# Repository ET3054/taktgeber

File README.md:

Einstellbarer Rechtecksignalgenerator (Taktgeber)
1. Projektbeschreibung
Im Rahmen dieses Projekts wurde ein einstellbarer Rechtecksignalgenerator entwickelt. Ziel des Projekts ist die Erzeugung eines Rechtecksignals mit einstellbarer Frequenz und Ausgangsamplitude.
Die elektrische Schaltung wurde mit KiCad 9 entworfen. Anschließend wurde auf Grundlage des Schaltplans eine vierlagige Leiterplatte (PCB) entwickelt.
Das Projekt umfasst den Schaltplan, das Leiterplattenlayout, die Bauteilliste (BOM) sowie die zugehörigen Fertigungsdaten.
2. Technische Daten
* Frequenzbereich: 1 Hz bis 1 kHz (Auslegungsziel)
* Ausgangsamplitude: 5 V bis 15 V (Auslegungsziel)
*Externe Versorgungsspannung:** 24 V DC oder ca. 17 V AC (Effektivwert, entsprechend 24 V Scheitelwert)
*Interne Versorgungsspannungen:** +18 V DC und +5 V DC
*Eingangsgleichrichtung:** Brückengleichrichter GBU4G mit anschließendem Glättungskondensator
* Leiterplatte: 4 Lagen
* Entwicklungssoftware: KiCad 9
3. Funktionsweise
3.1 Spannungsversorgung
Die Eingangsspannung wird zunächst über einen Brückengleichrichter (GBU4G) gleichgerichtet und anschließend durch einen Glättungskondensator stabilisiert.
Zwei Spannungsregler stellen die benötigten Versorgungsspannungen bereit:
* L7818CV: +18 V für die entsprechende Schaltungselektronik
* L7805CV: +5 V für den Mikrocontroller und das LCD
Zusätzlich wurde ein zweipoliger Anschluss J5 für einen externen Hauptschalter vorgesehen. Dieser ermöglicht die Unterbrechung einer Eingangsleitung vor dem Brückengleichrichter.
3.2 Signalerzeugung
Zur Erzeugung des Rechtecksignals wird der CMOS-Timer ICM7555IPAZ verwendet.
Die Frequenz wird über Widerstände, ein Potentiometer und umschaltbare Kondensatoren eingestellt.
Ein CD4013BE dient zur Frequenzteilung.
3.3 Einstellung der Ausgangsamplitude
Die Ausgangsstufe basiert auf einem LM358P.
Über ein Potentiometer wird die gewünschte Ausgangsamplitude eingestellt.
3.4 Mikrocontroller und Anzeige
Ein ATmega328P ist zur Verarbeitung der Signale und zur Ansteuerung eines 16×2-LCDs vorgesehen.
Das LCD dient zur Darstellung der relevanten Ausgangsgrößen.
Der Mikrocontroller soll separat programmiert und anschließend in seinen DIP-Sockel eingesetzt werden.
4. Leiterplattenaufbau
Die Leiterplatte wurde mit vier Kupferlagen entworfen:
Lage
Funktion
F.Cu
Signalleitungen und Versorgungsverbindungen
In1.Cu
GND-Fläche
In2.Cu
Getrennte Versorgungsflächen für +5 V und +18 V
B.Cu
Signalleitungen und Versorgungsverbindungen
Die Leiterplatte besitzt vier Montagebohrungen (H1–H4) zur mechanischen Befestigung.
Für die Hauptstromversorgung wurden entsprechend breitere Leiterbahnen vorgesehen.
5. Projektdateien
Das Repository enthält folgende Projekt- und Dokumentationsdateien:
* Flachbaugruppe.kicad_pro – KiCad-Projekteinstellungen
* Flachbaugruppe.kicad_sch – Elektrischer Schaltplan
* Flachbaugruppe.kicad_pcb – Vierlagiges Leiterplattenlayout
* Gerber/ – Gerber-Dateien, Bohrdateien und Bauteilpositionsdateien
* Flachbaugruppe_BOM_Final.csv – Aus KiCad exportierte Stückliste
* Rechtecksignalgenerator_BOM_Final.xlsx – Detaillierte Stückliste mit Hersteller- und Bauteilangaben
* Rechtecksignalgenerator_Fertigungsunterlagen.pdf – Fertigungs- und Bestückungsdokumentation
Die Fertigungsdokumentation wird an den aktuellen Entwicklungsstand angepasst.
6. Projektstatus
Der elektrische Schaltplan und das vierlagige Leiterplattenlayout wurden erstellt.
Im weiteren Entwicklungsverlauf wurde ein Anschluss für einen externen Hauptschalter (J5) ergänzt und in das PCB-Layout integriert.
Anschließend wurden die Leiterbahnen angepasst und die Design-Rule-Prüfung (DRC) durchgeführt.
Ergebnis der letzten DRC-Prüfung:
* 0 Leiterplattenverstöße
* 0 unverbundene Elemente
* 4 Hinweise zur Schaltplanparität aufgrund der ausschließlich auf der Leiterplatte vorhandenen Montagebohrungen H1–H4
Die Gerber-Dateien, Bohrdateien und Bauteilpositionsdateien wurden exportiert. Die Stückliste wurde aktualisiert.
Eine physische Fertigung und Bestückung der Leiterplatte sowie eine messtechnische Funktionsprüfung wurden bisher nicht durchgeführt.
7. Fazit
Im Rahmen des Projekts wurde ein vollständiger Schaltungsentwurf mit zugehörigem vierlagigem Leiterplattenlayout für einen einstellbaren Rechtecksignalgenerator erarbeitet.
Die Entwicklung umfasst die Spannungsversorgung, Signalerzeugung, Frequenzteilung, Ausgangsstufe sowie die vorgesehene Mikrocontroller- und LCD-Anbindung.
Die Projektdateien stehen zur weiteren Überprüfung, Weiterentwicklung und gegebenenfalls späteren Fertigung zur Verfügung.

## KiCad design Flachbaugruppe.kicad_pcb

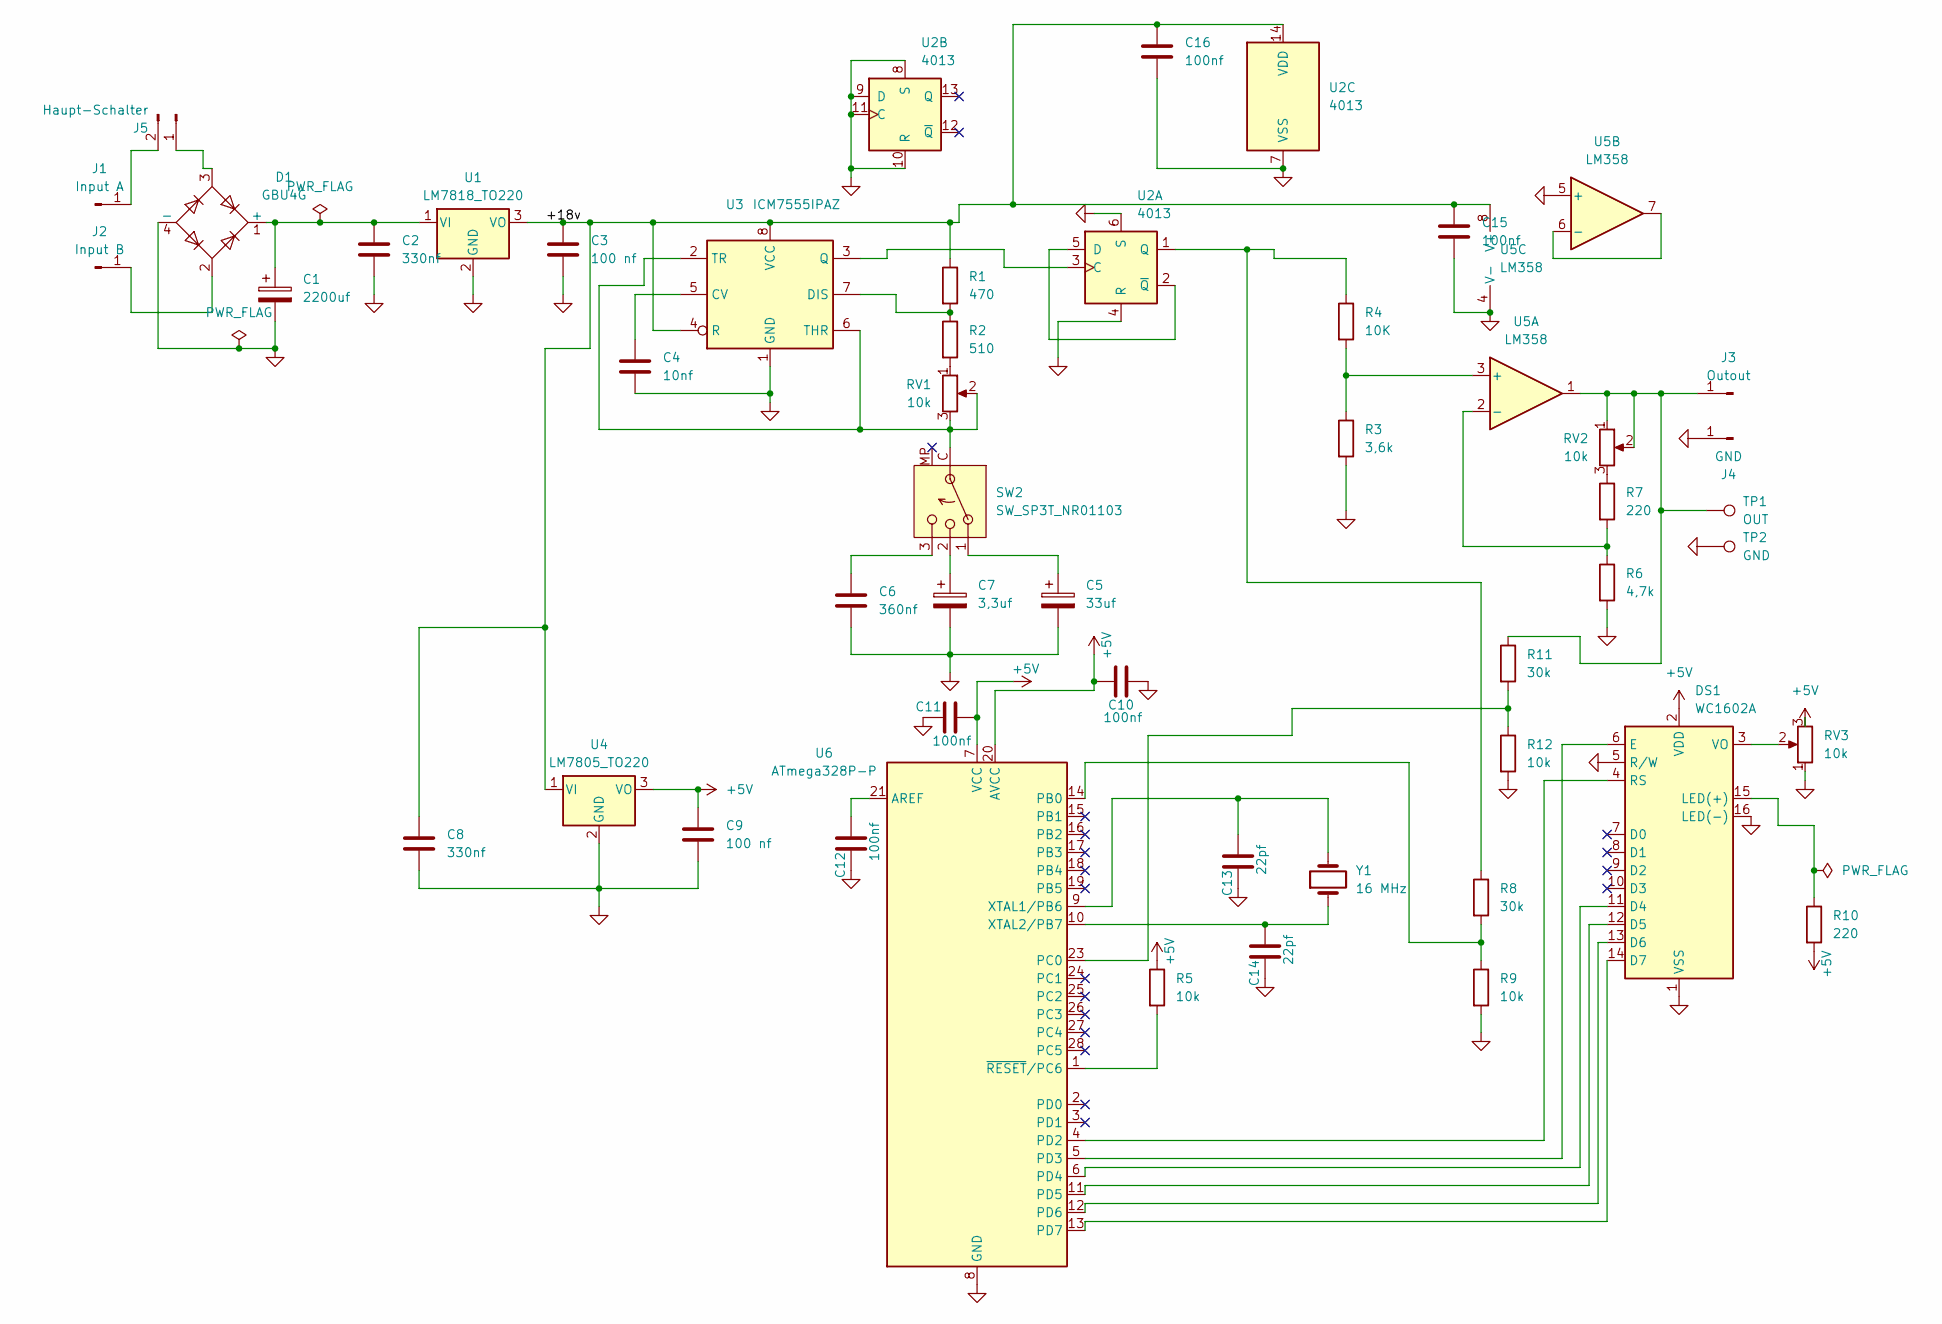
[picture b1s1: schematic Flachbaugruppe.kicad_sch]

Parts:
C1: 2200uf; CP_Radial_D16.0mm_P7.50mm
C2, C8: 330nf; C_0805_2012Metric
C3, C9: 100 nf; C_0805_2012Metric
C4: 10nf; C_0805_2012Metric
C5: 33uf; CP_Radial_D6.3mm_P2.50mm
C6: 360nf; C_0805_2012Metric
C7: 3,3uf; CP_Radial_D5.0mm_P2.00mm
C10, C11, C12, C15, C16: 100nf; C_0805_2012Metric
C13, C14: 22pf; C_0805_2012Metric
D1: GBU4G; Diode_Bridge_Vishay_GBU
DS1: WC1602A
J1: Input A; Banana_Jack_1Pin
J2: Input B; Banana_Jack_1Pin
J3: Outout; Banana_Jack_1Pin
J4: GND; Banana_Jack_1Pin
J5: Haupt-Schalter; TerminalBlock_MaiXu_MX126-5.0-02P_1x02_P5.00mm
R1: 470; R_0805_2012Metric
R2: 510; R_0805_2012Metric
R3: 3,6k; R_0805_2012Metric
R4: 10K; R_0805_2012Metric
R5, R9, R12: 10k; R_0805_2012Metric
R6: 4,7k; R_0805_2012Metric
R7, R10: 220; R_0805_2012Metric
R8, R11: 30k; R_0805_2012Metric
RV1, RV2: 10k; Potentiometer_Alps_RK09K_Single_Vertical
RV3: 10k; Potentiometer_Bourns_3296W_Vertical
SW2: SW_SP3T_NR01103; SW_NKK_NR01
TP1: OUT; TestPoint_Loop_D2.50mm_Drill1.0mm
TP2: GND; TestPoint_Loop_D2.50mm_Drill1.0mm
U1: LM7818_TO220; TO-220-3_Vertical
U2: 4013; DIP-14_W7.62mm
U3: ICM7555IPAZ; DIP-8_W7.62mm
U4: LM7805_TO220; TO-220-3_Vertical
U5: LM358; DIP-8_W7.62mm
U6: ATmega328P-P; DIP-28_W7.62mm
Y1: 16 MHz; Crystal_HC49-U_Vertical

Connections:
+5V: C9.1, C10.1, C11.2, DS1.2 (VDD), R5.1, R10.2, RV3.3, U4.3 (VO), U6.7 (VCC), U6.20 (AVCC)
/+18v: C3.1, C8.1, C15.1, C16.1, R1.1, U1.3 (VO), U2.14 (VDD), U3.4 (R), U3.8 (VCC), U4.1 (VI), U5.8 (V+)
GND: C1.2, C2.2, C3.2, C4.2, C5.2, C6.2, C7.2, C8.2, C9.2, C10.2, C11.1, C12.1, C13.1, C14.1, C15.2, C16.2, D1.4 (-), DS1.1 (VSS), DS1.5 (R/W), DS1.16 (LED(-)), J4.1, R3.2, R6.2, R9.2, R12.2, RV3.1, TP2.1, U1.2 (GND), U2.4 (R), U2.6 (S), U2.7 (VSS), U2.8 (S), U2.9 (D), U2.10 (R), U2.11 (C), U3.1 (GND), U4.2 (GND), U5.4 (V-), U5.5 (+), U6.8 (GND), U6.22 (GND)
unnamed: C5.1, SW2.1
unnamed: C6.1, SW2.3
unnamed: C7.1, SW2.2
unnamed: C1.1, C2.1, D1.1 (+), U1.1 (VI)
unnamed: DS1.11 (D4), U6.6 (PD4)
unnamed: DS1.12 (D5), U6.11 (PD5)
unnamed: DS1.13 (D6), U6.12 (PD6)
unnamed: DS1.14 (D7), U6.13 (PD7)
unnamed: DS1.6 (E), U6.5 (PD3)
unnamed: DS1.15 (LED(+)), R10.1
unnamed: DS1.4 (RS), U6.4 (PD2)
unnamed: DS1.3 (VO), RV3.2
unnamed: J1.1, J5.2
unnamed: D1.2, J2.1
unnamed: J3.1, R11.1, RV2.1, RV2.2, TP1.1, U5.1
unnamed: D1.3, J5.1
unnamed: R2.2, RV1.1
unnamed: R7.1, RV2.3
unnamed: RV1.2, RV1.3, SW2.C (Common), U3.2 (TR), U3.6 (THR)
unnamed: U2.3 (C), U3.3 (Q)
unnamed: U2.2 (~Q), U2.5 (D)
unnamed: R4.1, R8.1, U2.1 (Q)
unnamed: C4.1, U3.5 (CV)
unnamed: R1.2, R2.1, U3.7 (DIS)
unnamed: R3.1, R4.2, U5.3 (+)
unnamed: R6.1, R7.2, U5.2 (-)
unnamed: U5.6 (-), U5.7
unnamed: C12.2, U6.21 (AREF)
unnamed: R8.2, R9.1, U6.14 (PB0)
unnamed: R11.2, R12.1, U6.23 (PC0)
unnamed: C13.2, U6.9 (XTAL1/PB6), Y1.2
unnamed: C14.2, U6.10 (XTAL2/PB7), Y1.1
unnamed: R5.2, U6.1 (~RESET/PC6)

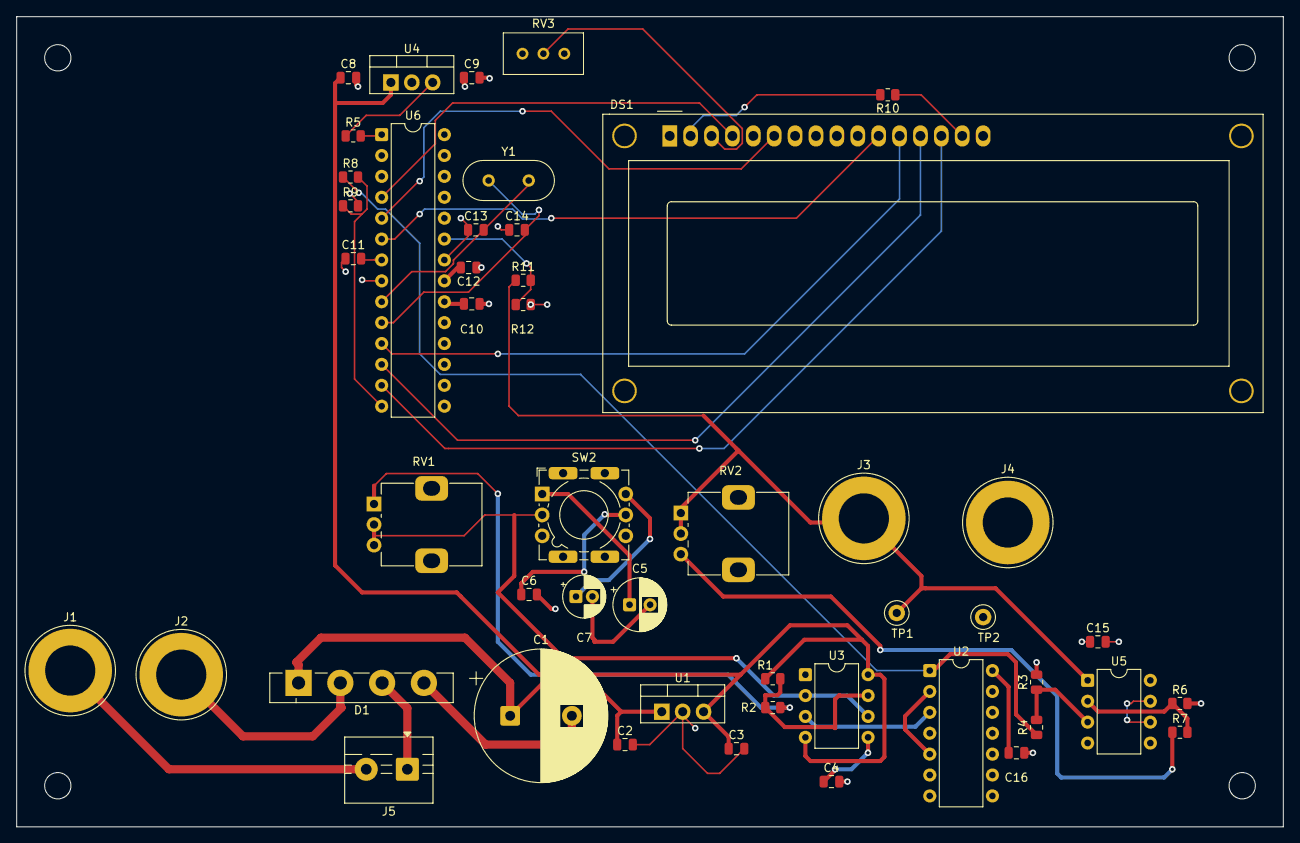
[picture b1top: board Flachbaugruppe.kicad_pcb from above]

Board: 4 copper layers, 154.0 x 98.5 mm, 52 parts (0 on the bottom side), 36 nets.

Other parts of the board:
H1, H2, H3, H4: MountingHole_3.2mm_M3

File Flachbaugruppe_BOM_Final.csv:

"ID";"Bezeichner";"Footprint";"Stückzahl";"Bezeichnung";"Anbieter und Referenz";
1;"J5";"TerminalBlock_MaiXu_MX126-5.0-02P_1x02_P5.00mm";1;"Haupt-Schalter";;;
2;"J2";"Banana_Jack_1Pin";1;"Input B";;;
3;"R11,R8";"R_0805_2012Metric";2;"30k";;;
4;"C4";"C_0805_2012Metric";1;"10nf";;;
5;"DS1";"WC1602A";1;"WC1602A";;;
6;"C8,C2";"C_0805_2012Metric";2;"330nf";;;
7;"R12,R9,R5";"R_0805_2012Metric";3;"10k";;;
8;"J1";"Banana_Jack_1Pin";1;"Input A";;;
9;"TP1";"TestPoint_Loop_D2.50mm_Drill1.0mm";1;"OUT";;;
10;"J3";"Banana_Jack_1Pin";1;"Outout";;;
11;"RV2,RV1";"Potentiometer_Alps_RK09K_Single_Horizontal";2;"10k";;;
12;"U3";"DIP-8_W7.62mm";1;"ICM7555IPAZ";;;
13;"U1";"TO-220-3_Vertical";1;"LM7818_TO220";;;
14;"U4";"TO-220-3_Vertical";1;"LM7805_TO220";;;
15;"R10,R7";"R_0805_2012Metric";2;"220";;;
16;"R6";"R_0805_2012Metric";1;"4,7k";;;
17;"U5";"DIP-8_W7.62mm";1;"LM358";;;
18;"C15,C11,C12,C16,C10";"C_0805_2012Metric";5;"100nf";;;
19;"TP2";"TestPoint_Loop_D2.50mm_Drill1.0mm";1;"GND";;;
20;"R2";"R_0805_2012Metric";1;"510";;;
21;"C6";"C_0805_2012Metric";1;"360nf";;;
22;"C7";"CP_Radial_D5.0mm_P2.00mm";1;"3,3uf";;;
23;"C5";"CP_Radial_D6.3mm_P2.50mm";1;"33uf";;;
24;"U2";"DIP-14_W7.62mm";1;"4013";;;
25;"Y1";"Crystal_HC49-U_Vertical";1;"16 MHz";;;
26;"C13,C14";"C_0805_2012Metric";2;"22pf";;;
27;"J4";"Banana_Jack_1Pin";1;"GND";;;
28;"C3,C9";"C_0805_2012Metric";2;"100 nf";;;
29;"R3";"R_0805_2012Metric";1;"3,6k";;;
30;"C1";"CP_Radial_D16.0mm_P7.50mm";1;"2200uf";;;
31;"RV3";"Potentiometer_Bourns_3296W_Vertical";1;"10k";;;
32;"R1";"R_0805_2012Metric";1;"470";;;
33;"SW2";"SW_NKK_NR01";1;"SW_SP3T_NR01103";;;
34;"R4";"R_0805_2012Metric";1;"10K";;;
35;"U6";"DIP-28_W7.62mm";1;"ATmega328P-P";;;
36;"D1";"Diode_Bridge_Vishay_GBU";1;"GBU4G";;;
